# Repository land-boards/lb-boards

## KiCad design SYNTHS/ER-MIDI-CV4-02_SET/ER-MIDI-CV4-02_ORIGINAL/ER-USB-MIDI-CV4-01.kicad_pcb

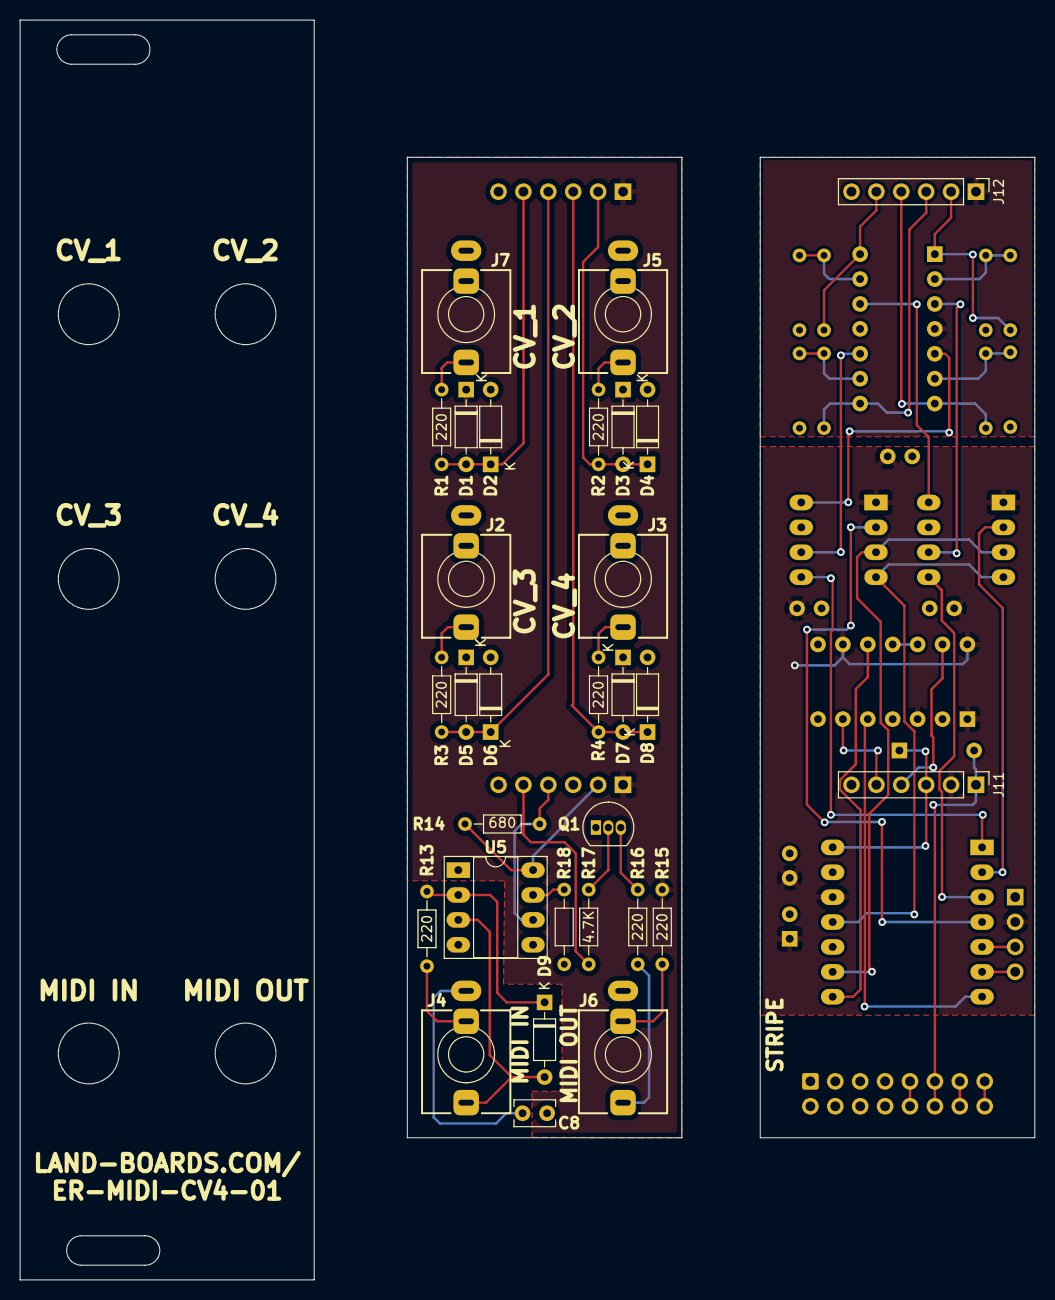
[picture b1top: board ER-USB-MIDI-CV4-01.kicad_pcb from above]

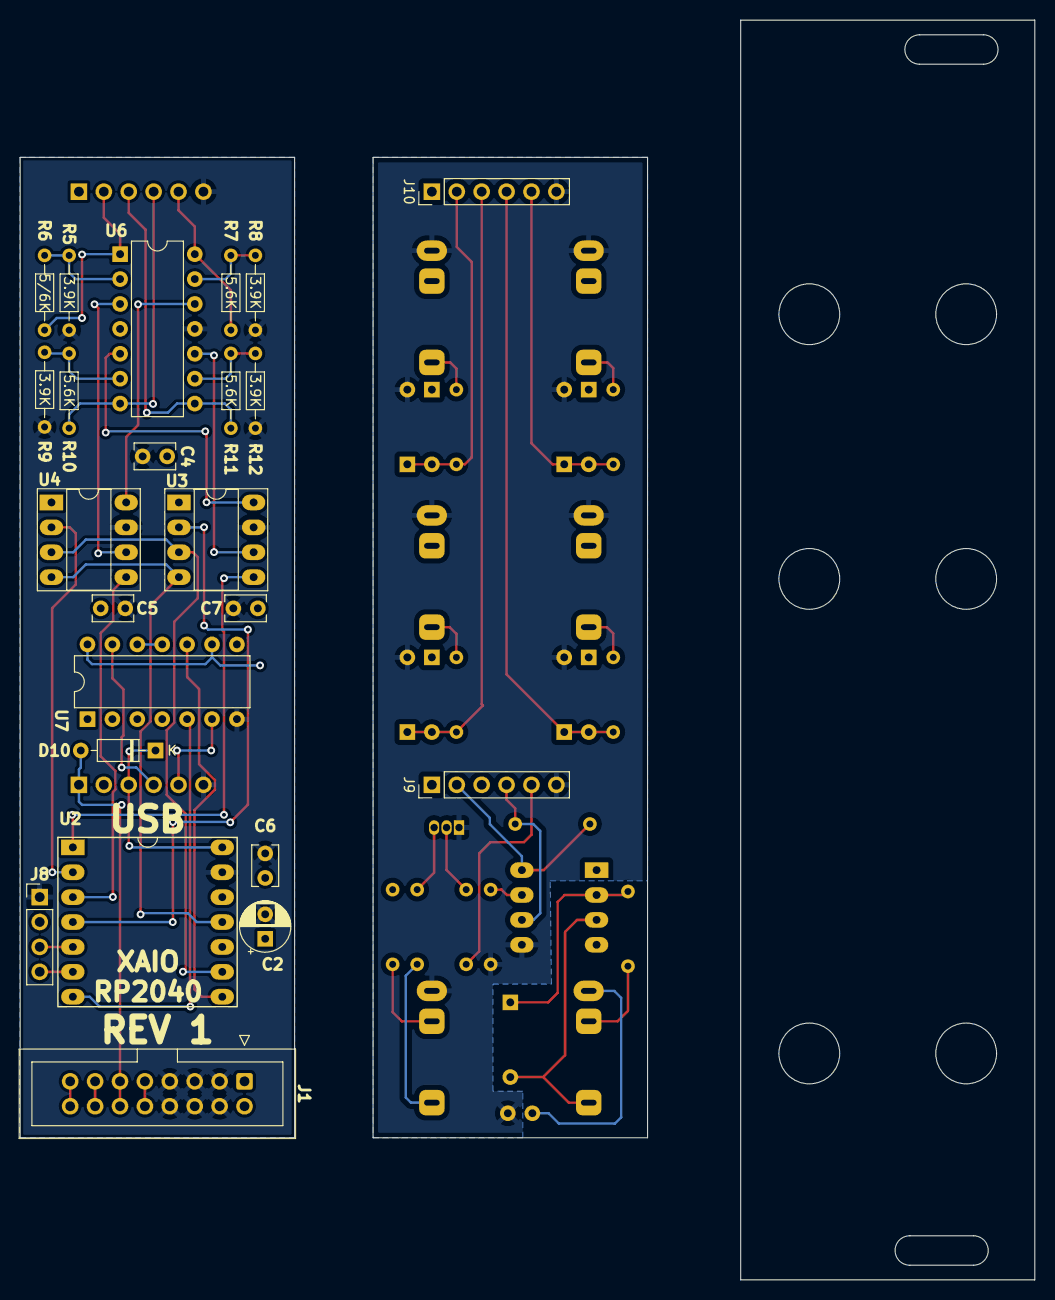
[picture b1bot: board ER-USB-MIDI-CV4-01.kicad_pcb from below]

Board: 2 copper layers, 103.5 x 128.5 mm, 53 parts (23 on the bottom side), 51 nets.

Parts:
C2: 10uF; CP_Radial_D5.0mm_P2.50mm
C4, C5, C6, C7, C8: 0.1uF; C_Rect_L4.0mm_W2.5mm_P2.50mm
D1, D2, D3, D4, D5, D6, D7, D8, D9, D10: BAT41; D_DO-35_SOD27_P7.62mm_Horizontal
J1: Conn_02x08_Odd_Even; IDC-Header_2x08_P2.54mm_Vertical
J2, J3, J4, J5, J6, J7: AudioJack3; Jack_3.5mm_QingPu_WQP-PJ366ST_Vertical
J8: Conn_01x04; PinHeader_1x04_P2.54mm_Vertical
J9, J10, J11, J12: Conn_01x06; PinHeader_1x06_P2.54mm_Vertical
Q1: 2N3904; TO-92_Inline
R1, R2, R3, R4, R13, R15, R16: 220; R_Axial_DIN0204_L3.6mm_D1.6mm_P7.62mm_Horizontal
R5, R8, R9, R12: 3.9K; R_Axial_DIN0204_L3.6mm_D1.6mm_P7.62mm_Horizontal
R6: 5/6K; R_Axial_DIN0204_L3.6mm_D1.6mm_P7.62mm_Horizontal
R7, R10, R11: 5.6K; R_Axial_DIN0204_L3.6mm_D1.6mm_P7.62mm_Horizontal
R14: 680; R_Axial_DIN0204_L3.6mm_D1.6mm_P7.62mm_Horizontal
R17: 4.7K; R_Axial_DIN0204_L3.6mm_D1.6mm_P7.62mm_Horizontal
R18: 1K; R_Axial_DIN0204_L3.6mm_D1.6mm_P7.62mm_Horizontal
U2: XIAO_RP2040; QT_Py
U3, U4: MCP4822-E/P; DIP-8_W7.62mm_Socket_LongPads
U5: 6N138; DIP-8_W7.62mm_Socket_LongPads
U6: MCP6234; DIP-14_W7.62mm
U7: 74HC14; DIP-14_W7.62mm

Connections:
+3V3: C2.1, C4.1, C5.1, C6.1, C7.1, J8.2, J9.2, J11.2, R14.2, U2.12 (3.3V), U3.1 (Vdd), U4.1 (Vdd), U5.8 (VCC), U7.1, U7.3, U7.9, U7.14 (VCC)
+5V: D1.1 (K), D3.1 (K), D5.1 (K), D7.1 (K), D10.2 (A), J1.11, J1.12, J9.1, J10.1, J11.1, J12.1, R15.2, U6.4 (V+)
+5VD: D10.1 (K), J9.3, J11.3, U2.14 (5V)
+12V: J1.9, J1.10
/AOUT1: U4.8 (VA), U6.12 (+)
/AOUT2: U4.6 (VB), U6.3 (+)
/AOUT3: U3.8 (VA), U6.5 (+)
/AOUT4: U3.6 (VB), U6.10 (+)
/CS12*: U2.2 (D1/P27), U4.2 (~CS)
/CS34*: U2.4 (D3/P29), U3.2 (~CS)
/CV1: J7.T, R1.2
/CV1_C: D1.2 (A), D2.1 (K), J10.5, R1.1
/CV1_D: J12.5, R7.2, U6.14
/CV2: J5.T, R2.2
/CV2_C: D3.2 (A), D4.1 (K), J10.2, R2.1
/CV2_D: J12.2, R6.2, U6.1
/CV3: J2.T, R3.2
/CV3_C: D5.2 (A), D6.1 (K), J10.4, R3.1
/CV3_D: J12.4, R10.2, U6.7
/CV4: J3.T, R4.2
/CV4_C: D7.2 (A), D8.1 (K), J10.3, R4.1
/CV4_D: J12.3, R11.2, U6.8
/CV_OUT: J1.13, J1.14
/GATE_OUT: J1.15, J1.16
/LD12*: U2.3 (D2/P28), U4.5 (~LDAC)
/LD34*: U2.1 (D0/P26), U3.5 (~LDAC)
/MIDI_GND: C8.1, J4.S
/MIDI_IN: J4.R, R13.1
/MIDI_RES: D9.1 (K), R13.2, U5.2 (C1)
/MIDI_RTN: D9.2 (A), J4.T, U5.3 (C2)
/MO5: J6.R, R15.1
/MOLO: J6.T, R16.2
/MOSI: U2.11 (D10/MOSI/P3), U3.4 (SDI), U4.4 (SDI)
/OBF: R18.1, U5.7 (VO1)
/OPTOUT-C: J9.4, R14.1, U5.6 (VO2)
/OPTOUT-D: J11.4, U7.13
/RBI-C: J9.5, R17.2
/RBI-D: J11.5, U7.6
/RBO: Q1.2 (B), R17.1
/RXD: U2.8 (D7/RX/P1), U7.10
/SCK: U2.9 (D8/SCK/P2), U3.3 (SCK), U4.3 (SCK)
GND: C2.2, C4.2, C5.2, C6.2, C7.2, C8.2, D2.2 (A), D4.2 (A), D6.2 (A), D8.2 (A), J1.3, J1.4, J1.5, J1.6, J1.7, J1.8, J2.S, J3.S, J5.S, J6.S, J7.S, J8.1, J9.6, J10.6, J11.6, J12.6, Q1.1 (E), R5.1, R8.1, R9.1, R12.1, R18.2, U2.13 (GND), U3.7 (Vss), U4.7 (Vss), U5.5 (GND), U6.11 (V-), U7.7 (GND)
unnamed: J8.3, U2.5 (D4/SDA/P6)
unnamed: J8.4, U2.6 (D5/SCL/P7)
unnamed: Q1.3 (C), R16.1
unnamed: R5.2, R6.1, U6.2 (-)
unnamed: R7.1, R8.2, U6.13 (-)
unnamed: R9.2, R10.1, U6.6 (-)
unnamed: R11.1, R12.2, U6.9 (-)
unnamed: U2.7 (D6/TX/P0), U7.5
unnamed: U7.11, U7.12

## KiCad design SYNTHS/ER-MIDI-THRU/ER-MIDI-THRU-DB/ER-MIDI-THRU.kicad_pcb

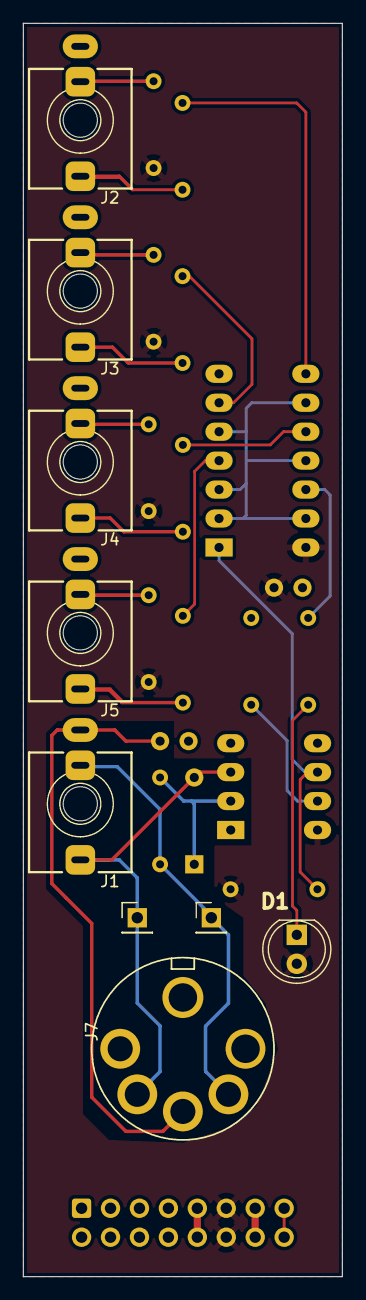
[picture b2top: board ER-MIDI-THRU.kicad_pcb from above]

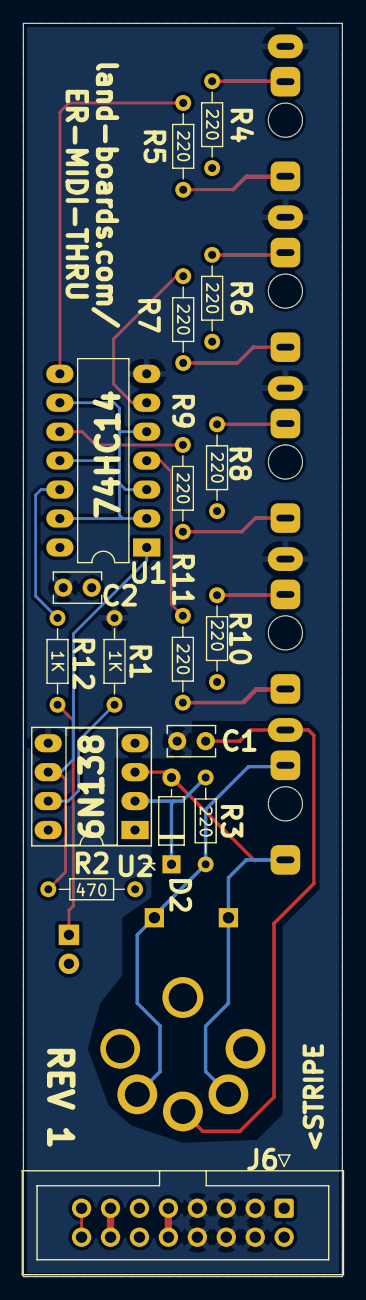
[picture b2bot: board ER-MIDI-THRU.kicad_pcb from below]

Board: 2 copper layers, 28.0 x 110.0 mm, 27 parts (18 on the bottom side), 26 nets.

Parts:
C1, C2: 0.1uF; C_Rect_L4.0mm_W2.5mm_P2.50mm
D1: LED; LED_D5.0mm
D2: 1N914; D_DO-35_SOD27_P7.62mm_Horizontal
J1, J2, J3, J4, J5: AudioJack3; PJ-366ST
J6: Conn_02x08_Odd_Even; IDC-Header_2x08_P2.54mm_Vertical
J7: DIN-5; DIN-5_SD-50BV-Vertical
J8, J9: Conn_01x01; PinHeader_1x01_P2.54mm_Vertical
R1, R12: 1K; R_Axial_DIN0204_L3.6mm_D1.6mm_P7.62mm_Horizontal
R2: 470; R_Axial_DIN0204_L3.6mm_D1.6mm_P7.62mm_Horizontal
R3, R4, R5, R6, R7, R8, R9, R10, R11: 220; R_Axial_DIN0204_L3.6mm_D1.6mm_P7.62mm_Horizontal
U1: 74HC14; DIP-14_W7.62mm_LongPads
U2: 6N138; DIP-8_W7.62mm_Socket_LongPads

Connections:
+5V: C2.1, D1.2 (A), J6.11, J6.12, R2.1, R4.1, R6.1, R8.1, R10.1, U1.14 (VCC), U2.8 (VCC)
+12V: J6.9, J6.10
/ALLRXD: U1.2, U1.3, U1.5, U1.9, U1.11, U1.13
/CV_OUT: J6.13, J6.14
/GATE_OUT: J6.15, J6.16
/MIDI_1_OUT: J2.T, R5.2
/MIDI_1_PWR: J2.R, R4.2
/MIDI_2_OUT: J3.T, R7.2
/MIDI_2_PWR: J3.R, R6.2
/MIDI_3_OUT: J4.T, R9.2
/MIDI_3_PWR: J4.R, R8.2
/MIDI_4_OUT: J5.T, R11.2
/MIDI_4_PWR: J5.R, R10.2
/MIDI_GND: C1.1, J1.S, J7.2
/MIDI_IN: J1.R, J7.4, J8.1, R3.2
/MIDI_RTN: D2.2 (A), J1.T, J7.5, J9.1, U2.3 (C2)
/RXD: R2.2, U1.1, U2.6 (VO2)
GND: C1.2, C2.2, J2.S, J3.S, J4.S, J5.S, J6.3, J6.4, J6.5, J6.6, J6.7, J6.8, R1.2, U1.7 (GND), U2.5 (GND)
unnamed: D1.1 (K), R12.2
unnamed: R1.1, U2.7 (VO1)
unnamed: D2.1 (K), R3.1, U2.2 (C1)
unnamed: R5.1, U1.8
unnamed: R7.1, U1.6
unnamed: R9.1, U1.10
unnamed: R11.1, U1.4
unnamed: R12.1, U1.12

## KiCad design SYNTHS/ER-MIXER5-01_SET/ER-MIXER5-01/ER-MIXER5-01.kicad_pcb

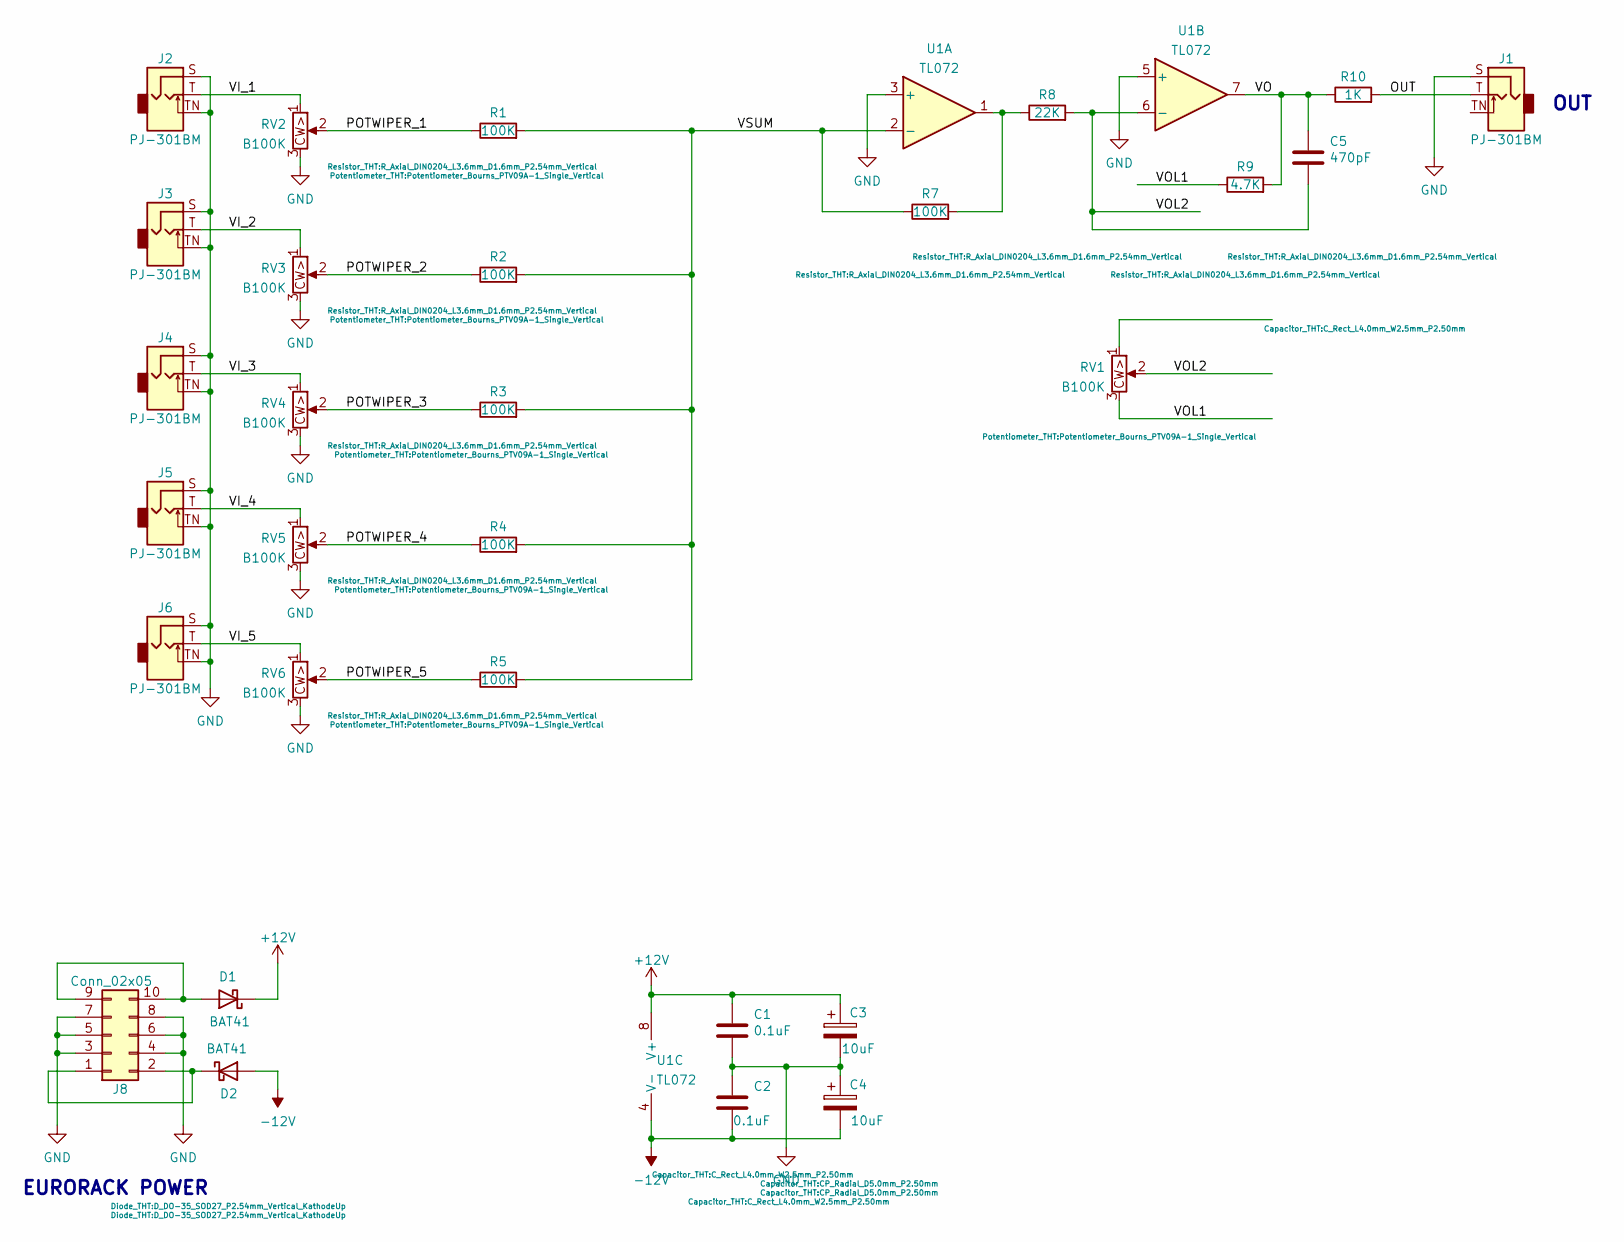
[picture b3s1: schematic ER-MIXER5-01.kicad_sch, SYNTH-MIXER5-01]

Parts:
C1, C2: 0.1uF; C_Rect_L4.0mm_W2.5mm_P2.50mm
C3, C4: 10uF; CP_Radial_D5.0mm_P2.50mm
C5: 470pF; C_Rect_L4.0mm_W2.5mm_P2.50mm
D1, D2: BAT41; D_DO-35_SOD27_P2.54mm_Vertical_KathodeUp
J1, J2, J3, J4, J5, J6: PJ-301BM; Jack_3.5mm_QingPu_WQP-PJ301BM_Vertical
J8: Conn_02x05; IDC-Header_2x05_P2.54mm_Vertical
R1, R2, R3, R4, R5, R7: 100K; R_Axial_DIN0204_L3.6mm_D1.6mm_P2.54mm_Vertical
R8: 22K; R_Axial_DIN0204_L3.6mm_D1.6mm_P2.54mm_Vertical
R9: 4.7K; R_Axial_DIN0204_L3.6mm_D1.6mm_P2.54mm_Vertical
R10: 1K; R_Axial_DIN0204_L3.6mm_D1.6mm_P2.54mm_Vertical
RV1, RV2, RV3, RV4, RV5, RV6: B100K; Potentiometer_Bourns_PTV09A-1_Single_Vertical
U1: TL072; DIP-8_W7.62mm

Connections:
+12V: C1.1, C3.1, D1.1 (K), U1.8 (V+)
-12V: C2.2, C4.2, D2.2 (A), U1.4 (V-)
/OUT: J1.T, R10.2
/POTWIPER_1: R1.1, RV2.2
/POTWIPER_2: R2.1, RV3.2
/POTWIPER_3: R3.1, RV4.2
/POTWIPER_4: R4.1, RV5.2
/POTWIPER_5: R5.1, RV6.2
/VI_1: J2.T, RV2.1
/VI_2: J3.T, RV3.1
/VI_3: J4.T, RV4.1
/VI_4: J5.T, RV5.1
/VI_5: J6.T, RV6.1
/VO: C5.1, R9.2, R10.1, U1.7
/VOL1: R9.1, RV1.3
/VOL2: C5.2, R8.2, RV1.2, U1.6 (-)
/VSUM: R1.2, R2.2, R3.2, R4.2, R5.2, R7.1, U1.2 (-)
GND: C1.2, C2.1, C3.2, C4.1, J1.S, J2.S, J2.TN, J3.S, J3.TN, J4.S, J4.TN, J5.S, J5.TN, J6.S, J6.TN, J8.3, J8.4, J8.5, J8.6, J8.7, J8.8, RV2.3, RV3.3, RV4.3, RV5.3, RV6.3, U1.3 (+), U1.5 (+)
unnamed: D2.1 (K), J8.1, J8.2
unnamed: D1.2 (A), J8.9, J8.10
unnamed: R7.2, R8.1, U1.1

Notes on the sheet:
EURORACK POWER
OUT

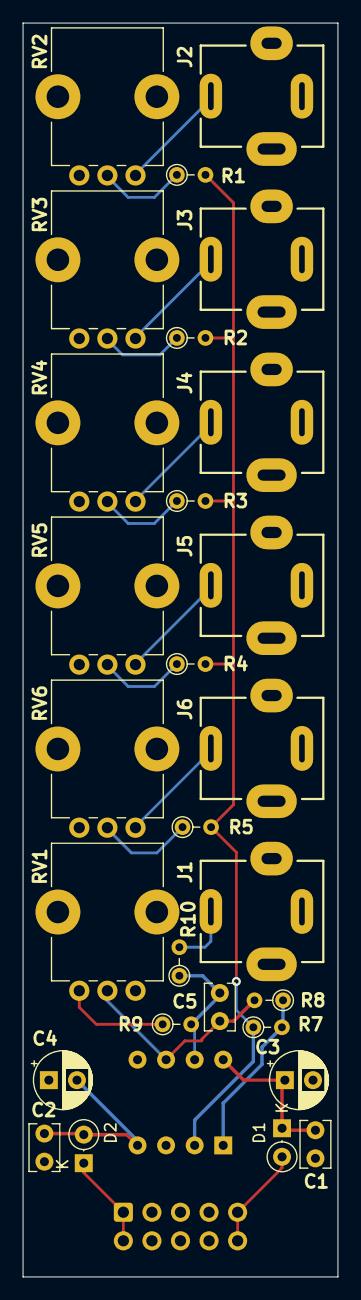
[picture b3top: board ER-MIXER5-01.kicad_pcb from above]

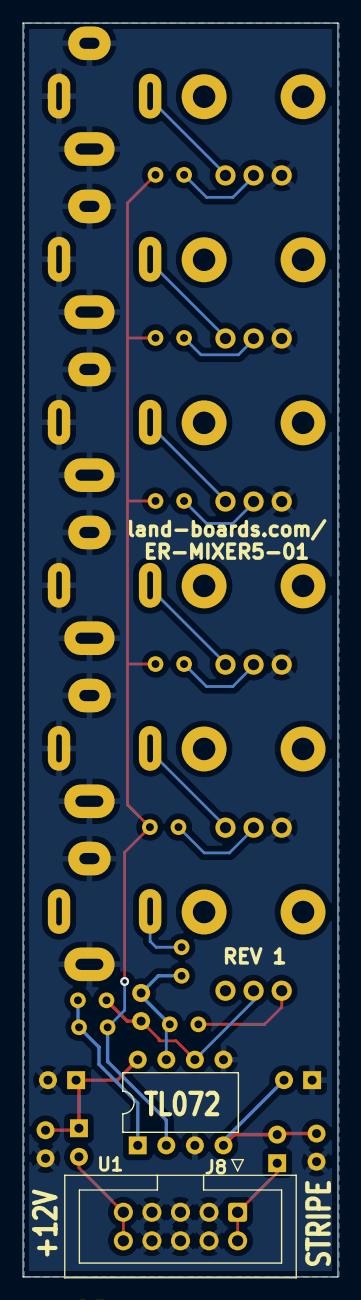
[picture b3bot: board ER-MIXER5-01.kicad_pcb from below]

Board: 2 copper layers, 28.0 x 111.5 mm, 30 parts (2 on the bottom side), 21 nets.
